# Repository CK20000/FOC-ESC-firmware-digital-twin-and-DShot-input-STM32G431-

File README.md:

# FOC ESC: firmware, digital twin and DShot input (STM32G431)

Sensorless field-oriented control (FOC) firmware for a custom 6S drone ESC, together with a software-in-the-loop (SIL) digital twin that runs the same C code against a simulated motor, inverter and PCB.

**Status:** the firmware and the DShot input have been tested on a bare STM32G431 dev board. The ESC PCB in this repository has passed DFM checks but has not been manufactured yet, so nothing here has been run on a motor.

## What is in this repository

- **Firmware (`Src/`, `Inc/`)**: 48 kHz sensorless FOC with a sliding-mode observer (SMO), a PLL, I-f startup and space vector PWM. The time-critical code runs from CCM RAM.
- **DShot300 receiver (`Src/foc_dshot.c`)**: a raw 32-edge decoder on PA0, written from scratch.
- **Digital twin (`sim/`)**: a C plant model (PMSM, inverter dead-time, Rds(on) drops, battery sag) plus a Python solver for PCB heat and ground bounce, shown in a PyQt6 dashboard.
- **Hardware (KiCad project and Gerbers)**: a 4-layer board (F.Cu, In1.Cu, In2.Cu, B.Cu) built around an STM32G431, an EG2134 gate driver and AD8418 current-sense amplifiers.

## Layout

```text
Inc/
  foc_core.h         FOC API, state machine, debug struct
  foc_dshot.h        DShot API and receiver state
Src/
  foc_core.c         FOC algorithm (SMO, PLL, I-f startup, CCM RAM)
  foc_dshot.c        DShot300 receiver
  main.c             Hardware init, CCM copy routine, flash-readout benchmark
  usb_cdc.c          USB CDC support
sim/
  sil/               Firmware + C plant, built into a shared library
    plant_c.c/.h              plant model
    sim_bridge.c/.h           bridge between the plant and Python
    virtual_stm32.c/.h        x86 stand-in for the MCU
    streaming_scope4.py       PyQt6 dashboard
  hil/               PCB thermal and ground-bounce solvers
    unified_esc_dashboard.py
    pcb_geometry.json
  test_dshot.py, virtual_mcu_dshot.py   DShot decoder tests on a virtual MCU
Makefile.hardware    Builds the .elf/.bin for the STM32G431
foc_g431.ld          Linker script with a CCM RAM section
```

## Quick start: simulation

```bash
cd sim/sil
make clean && make
python3 streaming_scope4.py
```

Press **Play**, raise the **Throttle** slider, and raise the **Speed** slider to speed up the simulation.

## Quick start: hardware

Install the ARM toolchain and a DFU tool:

```bash
sudo apt install gcc-arm-none-eabi dfu-util
```

Build from the folder that contains `Makefile.hardware`:

```bash
make -f Makefile.hardware clean
make -f Makefile.hardware -j4
```

This writes `build_hardware/foc_g431.elf`, `.bin` and `.map`.

Flash over USB DFU:

1. Hold **BOOT0**, tap **RESET**, release **BOOT0**.
2. Under WSL, attach the USB device first (Windows PowerShell, as admin): `usbipd list`, then `usbipd attach --wsl --busid <BUSID>`.
3. Flash:

```bash
sudo dfu-util --device 0483:df11 --alt 0 --dfuse-address 0x08000000:leave --download build_hardware/foc_g431.bin
```

The final `Error during download get_status` message is expected, since the board reboots after flashing.

## Measurements on silicon

`main.c` runs `foc_loop()` for 5 seconds (240,000 iterations), records the worst-case cycle count with the `DWT->CYCCNT` register, and saves a debug record to the last flash page (`0x0801F800`). Read it back with:

```bash
rm -f debug.bin
sudo dfu-util --device 0483:df11 --alt 0 --dfuse-address 0x0801F800:40 --upload debug.bin
hexdump -e '5/4 "%d " "\n"' debug.bin
```

The record is the `DebugInfo` struct in `foc_core.h`:

| Field | Meaning |
| :--- | :--- |
| `magic` | `0xDEADBEEF` if the record is valid |
| `loop_count` | Number of loop iterations run |
| `final_state` | Drive state at the end (0 = OFF, 3 = closed-loop FOC) |
| `throttle_x1000` | Throttle times 1000 (800 means 0.8) |
| `max_cycles` | Worst-case cycles for one loop |

Results so far, both on a dev board with no motor attached:

| Run | Final state | Throttle | Worst-case cycles | Time at 170 MHz |
| :--- | :--- | :--- | :--- | :--- |
| Closed-loop benchmark (forced closed-loop state) | 3 | 0.800 | 1,224 | 7.2 µs |
| DShot input test (DShot command from a flight controller) | 0 (OFF) | 0.480 | 1,162 | 6.8 µs |

The 1,224-cycle figure is the one to use for the closed-loop budget. The DShot run stayed in the OFF state, so its 1,162 cycles do not include the closed-loop control math. What the DShot run shows is that a throttle command sent by a flight controller reached the FOC core.

## DShot300 input

A DShot frame is 16 bits (11 throttle, 1 telemetry request, 4 CRC), which gives 32 edges per frame. At DShot300 each bit lasts 3.33 µs. The decoder on PA0 timestamps each edge with the DWT cycle counter.

Problems found and fixed while testing on the dev board:

- **Wrong frame length.** The first decoder waited for 42 edges and used GCR decoding. GCR is used only for the ESC's replies in bidirectional DShot, so the old decoder spanned two frames. It now decodes the raw 32-edge frame.
- **Clock speed.** The Arduino core ran the chip at 150 MHz, not 170 MHz, so a fixed 0/1 threshold failed. The decoder now measures the bit period and sets the threshold from it.
- **CRC.** With bidirectional DShot enabled, Betaflight inverts the CRC. The decoder accepts both forms.
- **Interrupt priority.** Every second frame collided with the 1 kHz SysTick interrupt, which delayed the edge timestamp. Giving the EXTI edge interrupt a higher priority than SysTick fixed it.

The receiver keeps `frames_ok` and `frames_bad` counters in the `dshot` struct. A complete frame-error measurement over a full throttle sweep is still to be published.

## Simulation features

- **I-f startup:** forces current into the motor and rotates the field to drag the rotor from rest.
- **SMO + PLL:** sensorless angle estimate.
- **Inverter model:** 200 ns dead-time distortion, MOSFET Rds(on) drops, battery sag.
- **Thermal model:** finite-difference heat diffusion across the PCB copper layers, from conduction (I²R) and switching losses based on FET datasheets.
- **Ground bounce:** copper resistance extracted from the layout, with differential ground-bounce errors injected into the ADC measurements.

## Pinout

| Pin | Function | Description |
| :--- | :--- | :--- |
| PA0 | DShot input | From the flight controller |
| PA1 | Phase U | ADC1 current sense |
| PA7 | Phase V | ADC2 current sense |
| PA8 | U high | Gate driver |
| PA9 | V high | Gate driver |
| PA10 | W high | Gate driver |
| PB13 | U low | Gate driver |
| PB14 | V low | Gate driver |
| PB15 | W low | Gate driver |
| PA2 / PA3 | Telemetry TX / RX | USART2 at 2 Mbaud |
| PA13 / PA14 | SWDIO / SWCLK | Debug |

Telemetry is a binary 49-byte struct on USART2. If the board is wired for USART1 on PB6/PB7 instead, switch `MX_USART2_UART_Init` to `MX_USART1_UART_Init` with `GPIO_PIN_6 | GPIO_PIN_7` and `AF7_USART1`.

## Board status and next steps

- The 4-layer PCB has passed DFM checks against JLCPCB capabilities.
- Components are being sourced for the first board.
- Next: assemble the first board, check the DShot timing on PA0 with a scope, and do a current-limited bench bring-up before any motor test.

## Known limits

- The gate driver, current sensing, observer and PLL have not been tested on a real motor.
- The digital twin is only as accurate as its motor and inverter model.
- The dev-board tests used no motor, so the timing figures come from benchmark inputs, not from a spinning rotor.

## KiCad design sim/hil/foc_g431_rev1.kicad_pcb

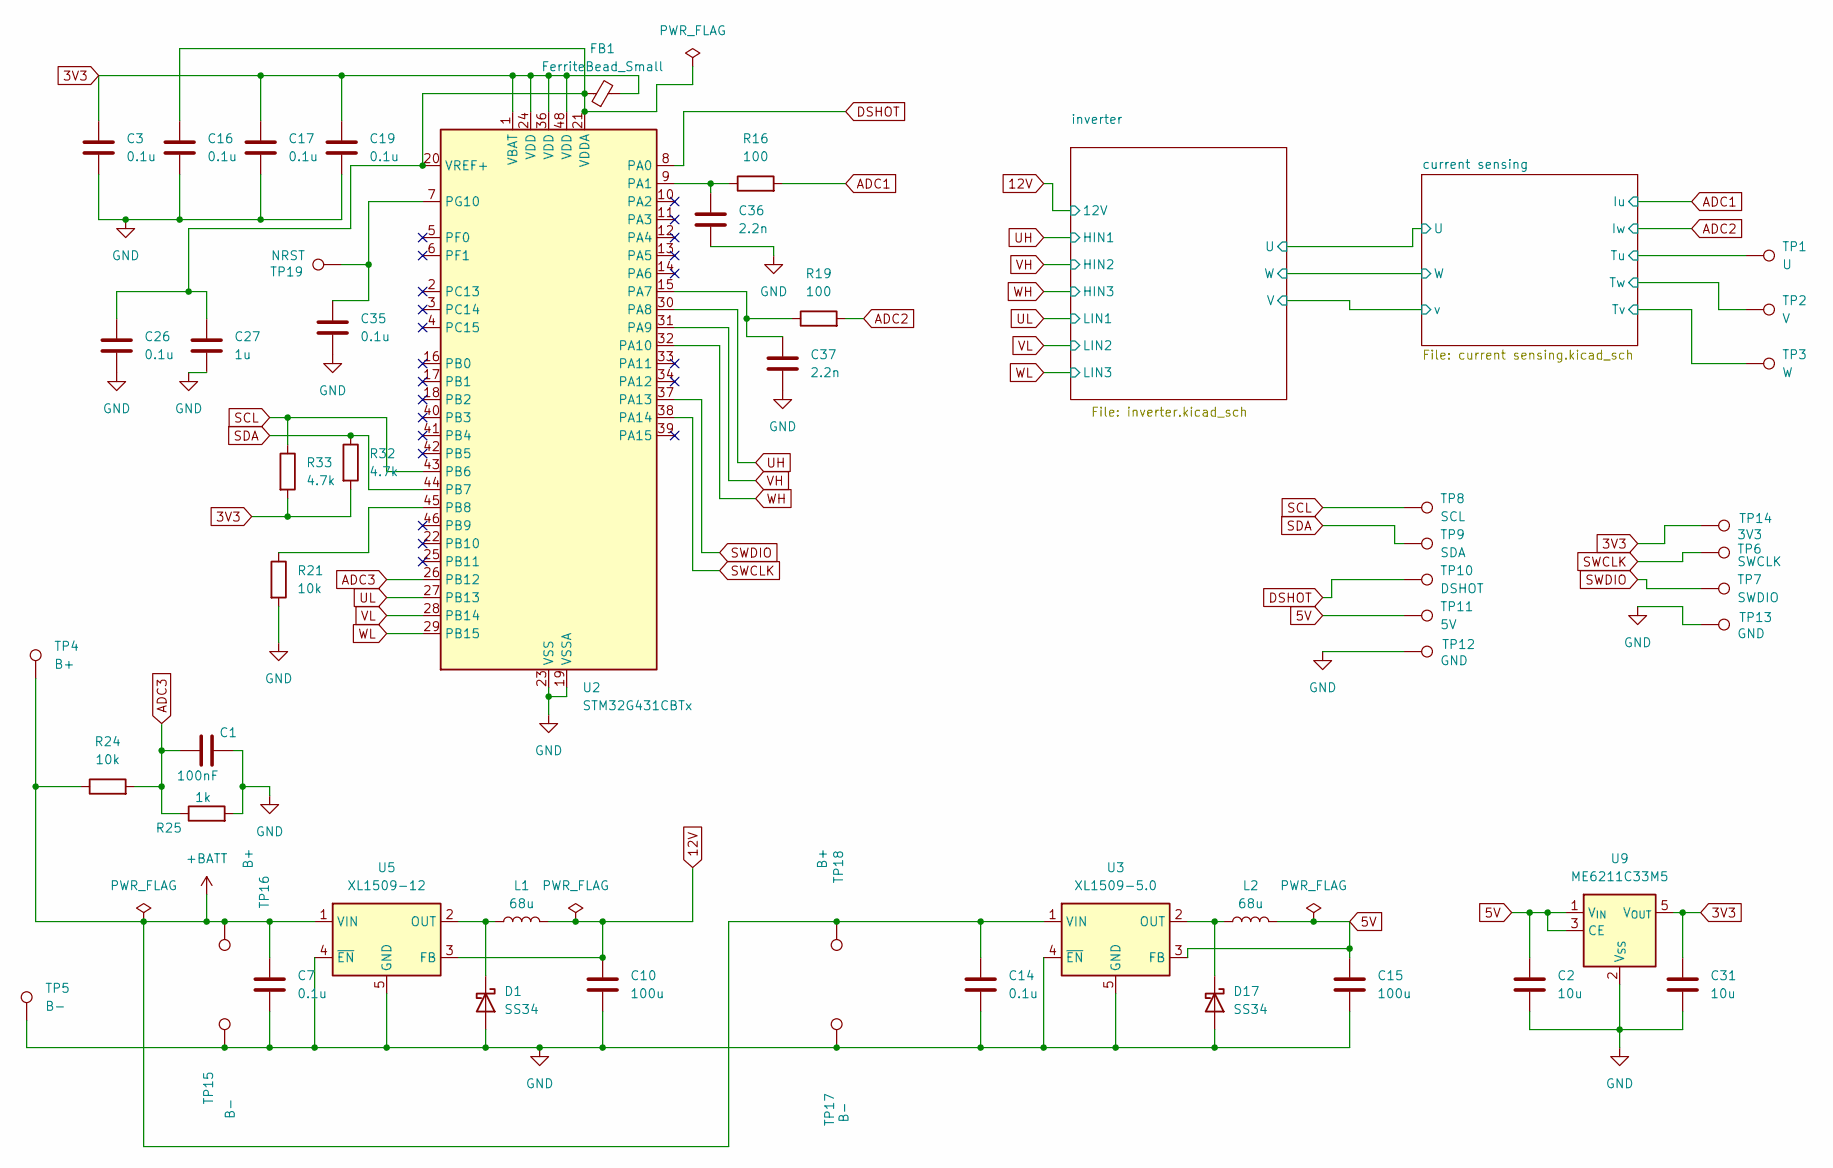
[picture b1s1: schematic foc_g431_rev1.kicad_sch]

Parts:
C1: 100nF; C_0603_1608Metric_Pad1.08x0.95mm_HandSolder
C2, C31: 10u; C_0805_2012Metric_Pad1.18x1.45mm_HandSolder
C3, C7, C14, C16, C17, C19, C26, C35: 0.1u; C_0603_1608Metric_Pad1.08x0.95mm_HandSolder
C10, C15: 100u; CP_EIA-3528-21_Kemet-B_HandSolder
C27: 1u; C_0603_1608Metric_Pad1.08x0.95mm_HandSolder
C36, C37: 2.2n; C_0603_1608Metric_Pad1.08x0.95mm_HandSolder
D1, D17: SS34; D_SMA
FB1: FerriteBead_Small; L_0805_2012Metric_Pad1.05x1.20mm_HandSolder
L1, L2: 68u; L_APV_APH0630
R16, R19: 100; R_0805_2012Metric_Pad1.20x1.40mm_HandSolder
R21, R24: 10k; R_0603_1608Metric_Pad0.98x0.95mm_HandSolder
R25: 1k; R_0603_1608Metric_Pad0.98x0.95mm_HandSolder
R32, R33: 4.7k; R_0603_1608Metric_Pad0.98x0.95mm_HandSolder
TP1: U; TestPoint_Pad_1.0x1.0mm
TP2: V; TestPoint_Pad_1.0x1.0mm
TP3: W; TestPoint_Pad_1.0x1.0mm
TP4, TP16, TP18: B+; TestPoint_Pad_1.0x1.0mm
TP5, TP15, TP17: B-; TestPoint_Pad_1.0x1.0mm
TP6: SWCLK; TestPoint_Pad_1.0x1.0mm
TP7: SWDIO; TestPoint_Pad_1.0x1.0mm
TP8: SCL; TestPoint_Pad_1.0x1.0mm
TP9: SDA; TestPoint_Pad_1.0x1.0mm
TP10: DSHOT; TestPoint_Pad_1.0x1.0mm
TP11: 5V; TestPoint_Pad_1.0x1.0mm
TP12, TP13: GND; TestPoint_Pad_1.0x1.0mm
TP14: 3V3; TestPoint_Pad_1.0x1.0mm
TP19: NRST; TestPoint_Pad_1.0x1.0mm
U2: STM32G431CBTx; LQFP-48_7x7mm_P0.5mm
U3: XL1509-5.0; SOIC-8_3.9x4.9mm_P1.27mm
U5: XL1509-12; SOIC-8_3.9x4.9mm_P1.27mm
U9: ME6211C33M5; SOT-23-5

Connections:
3V3: C3.1, C17.1, C19.1, C31.1, FB1.2, R32.2, R33.2, TP14.1, U2.1 (VBAT), U2.24 (VDD), U2.36 (VDD), U2.48 (VDD), U9.5 (V_{OUT}); also elsewhere on the board
5V: C2.1, C15.1, L2.2, TP11.1, U3.3 (FB), U9.1 (V_{IN}), U9.3 (CE)
12V: C10.1, L1.2, U5.3 (FB); also elsewhere on the board
+BATT: C7.1, C14.1, R24.1, TP4.1, TP16.1, TP18.1, U3.1 (VIN), U5.1 (VIN); also elsewhere on the board
/current sensing/Tu: TP1.1; also elsewhere on the board
/current sensing/Tv: TP3.1; also elsewhere on the board
/current sensing/Tw: TP2.1; also elsewhere on the board
ADC1: R16.2; also elsewhere on the board
ADC2: R19.2; also elsewhere on the board
ADC3: C1.2, R24.2, R25.1, U2.26 (PB12)
DSHOT: TP10.1, U2.8 (PA0)
GND: C1.1, C2.2, C3.2, C7.2, C10.2, C14.2, C15.2, C16.2, C17.2, C19.2, C26.2, C27.2, C31.2, C35.2, C36.2, C37.2, D1.2 (A), D17.2 (A), R21.2, R25.2, TP5.1, TP12.1, TP13.1, TP15.1, TP17.1, U2.19 (VSSA), U2.23 (VSS), U2.35 (VSS), U2.47 (VSS), U3.4 (~EN), U3.5 (GND), U3.6 (GND), U3.7 (GND), U3.8 (GND), U5.4 (~EN), U5.5 (GND), U5.6 (GND), U5.7 (GND), U5.8 (GND), U9.2 (V_{SS}); also elsewhere on the board
unnamed: D1.1 (K), L1.1, U5.2 (OUT)
unnamed: D17.1 (K), L2.1, U3.2 (OUT)
unnamed: C36.1, R16.1, U2.9 (PA1)
unnamed: C37.1, R19.1, U2.15 (PA7)
unnamed: R21.1, U2.45 (PB8)
unnamed: C35.1, TP19.1, U2.7 (PG10)
unnamed: C16.1, C26.1, C27.1, FB1.1, U2.20 (VREF+), U2.21 (VDDA)
SCL: R33.1, TP8.1, U2.43 (PB6)
SDA: R32.1, TP9.1, U2.44 (PB7)
SWCLK: TP6.1, U2.38 (PA14)
SWDIO: TP7.1, U2.37 (PA13)
UH: U2.30 (PA8); also elsewhere on the board
UL: U2.27 (PB13); also elsewhere on the board
VH: U2.31 (PA9); also elsewhere on the board
VL: U2.28 (PB14); also elsewhere on the board
WH: U2.32 (PA10); also elsewhere on the board
WL: U2.29 (PB15); also elsewhere on the board

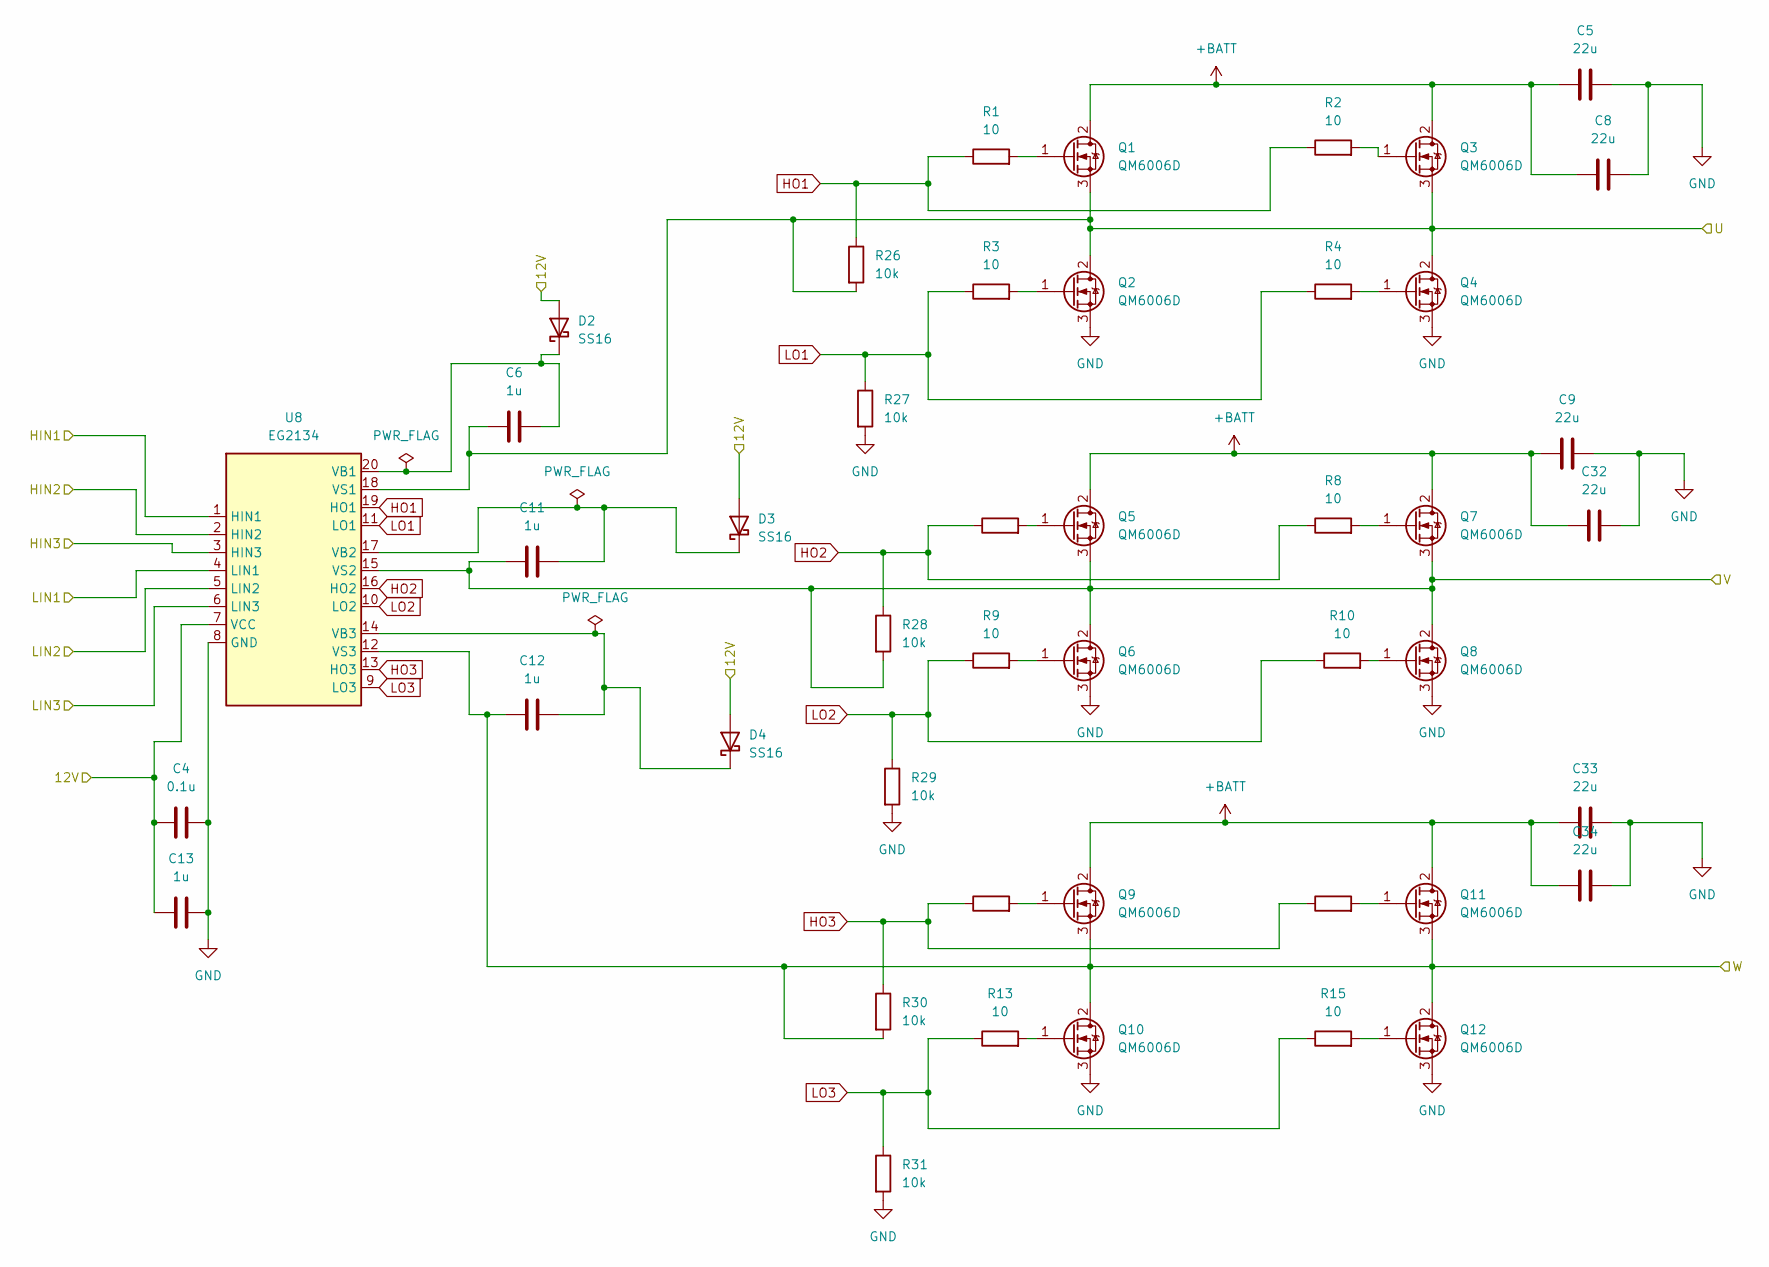
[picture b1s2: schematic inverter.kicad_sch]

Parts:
C4: 0.1u; C_0603_1608Metric_Pad1.08x0.95mm_HandSolder
C5, C8, C9, C32, C33, C34: 22u; C_1206_3216Metric_Pad1.33x1.80mm_HandSolder
C6, C11, C12, C13: 1u; C_0603_1608Metric_Pad1.08x0.95mm_HandSolder
D2, D3, D4: SS16; D_SMA
Q1, Q2, Q3, Q4, Q5, Q6, Q7, Q8, Q9, Q10, Q11, Q12: QM6006D; TO-252-2
R1, R2, R3, R4, R7, R8, R9, R10, R11, R12, R13, R15: 10; R_0603_1608Metric_Pad0.98x0.95mm_HandSolder
R26, R27, R28, R29, R30, R31: 10k; R_0603_1608Metric_Pad0.98x0.95mm_HandSolder
U8: EG2134; TSSOP-20_4.4x6.5mm_P0.65mm

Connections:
12V: C4.1, C13.2, D2.2 (A), D3.2 (A), D4.2 (A), U8.7 (VCC); also elsewhere on the board
+BATT: C5.1, C8.1, C9.1, C32.1, C33.1, C34.1, Q1.2 (D), Q3.2 (D), Q5.2 (D), Q7.2 (D), Q9.2 (D), Q11.2 (D); also elsewhere on the board
/current sensing/Tv: C11.1, Q5.3 (S), Q6.2 (D), Q7.3 (S), Q8.2 (D), R28.2, U8.15 (VS2); also elsewhere on the board
/current sensing/U: C6.2, Q1.3 (S), Q2.2 (D), Q3.3 (S), Q4.2 (D), R26.2, U8.18 (VS1); also elsewhere on the board
/current sensing/W: C12.1, Q9.3 (S), Q10.2 (D), Q11.3 (S), Q12.2 (D), R30.2, U8.12 (VS3); also elsewhere on the board
GND: C4.2, C5.2, C8.2, C9.2, C13.1, C32.2, C33.2, C34.2, Q2.3 (S), Q4.3 (S), Q6.3 (S), Q8.3 (S), Q10.3 (S), Q12.3 (S), R27.2, R29.2, R31.2, U8.8 (GND); also elsewhere on the board
HO1: R1.1, R2.1, R26.1, U8.19 (HO1)
HO2: R7.1, R8.1, R28.1, U8.16 (HO2)
HO3: R11.1, R12.1, R30.1, U8.13 (HO3)
LO1: R3.1, R4.1, R27.1, U8.11 (LO1)
LO2: R9.1, R10.1, R29.1, U8.10 (LO2)
LO3: R13.1, R15.1, R31.1, U8.9 (LO3)
unnamed: C6.1, D2.1 (K), U8.20 (VB1)
unnamed: C11.2, D3.1 (K), U8.17 (VB2)
unnamed: C12.2, D4.1 (K), U8.14 (VB3)
unnamed: Q1.1 (G), R1.2
unnamed: Q2.1 (G), R3.2
unnamed: Q3.1 (G), R2.2
unnamed: Q4.1 (G), R4.2
unnamed: Q5.1 (G), R7.2
unnamed: Q6.1 (G), R9.2
unnamed: Q7.1 (G), R8.2
unnamed: Q8.1 (G), R10.2
unnamed: Q9.1 (G), R11.2
unnamed: Q10.1 (G), R13.2
unnamed: Q11.1 (G), R12.2
unnamed: Q12.1 (G), R15.2
UH: U8.1 (HIN1); also elsewhere on the board
UL: U8.4 (LIN1); also elsewhere on the board
VH: U8.2 (HIN2); also elsewhere on the board
VL: U8.5 (LIN2); also elsewhere on the board
WH: U8.3 (HIN3); also elsewhere on the board
WL: U8.6 (LIN3); also elsewhere on the board

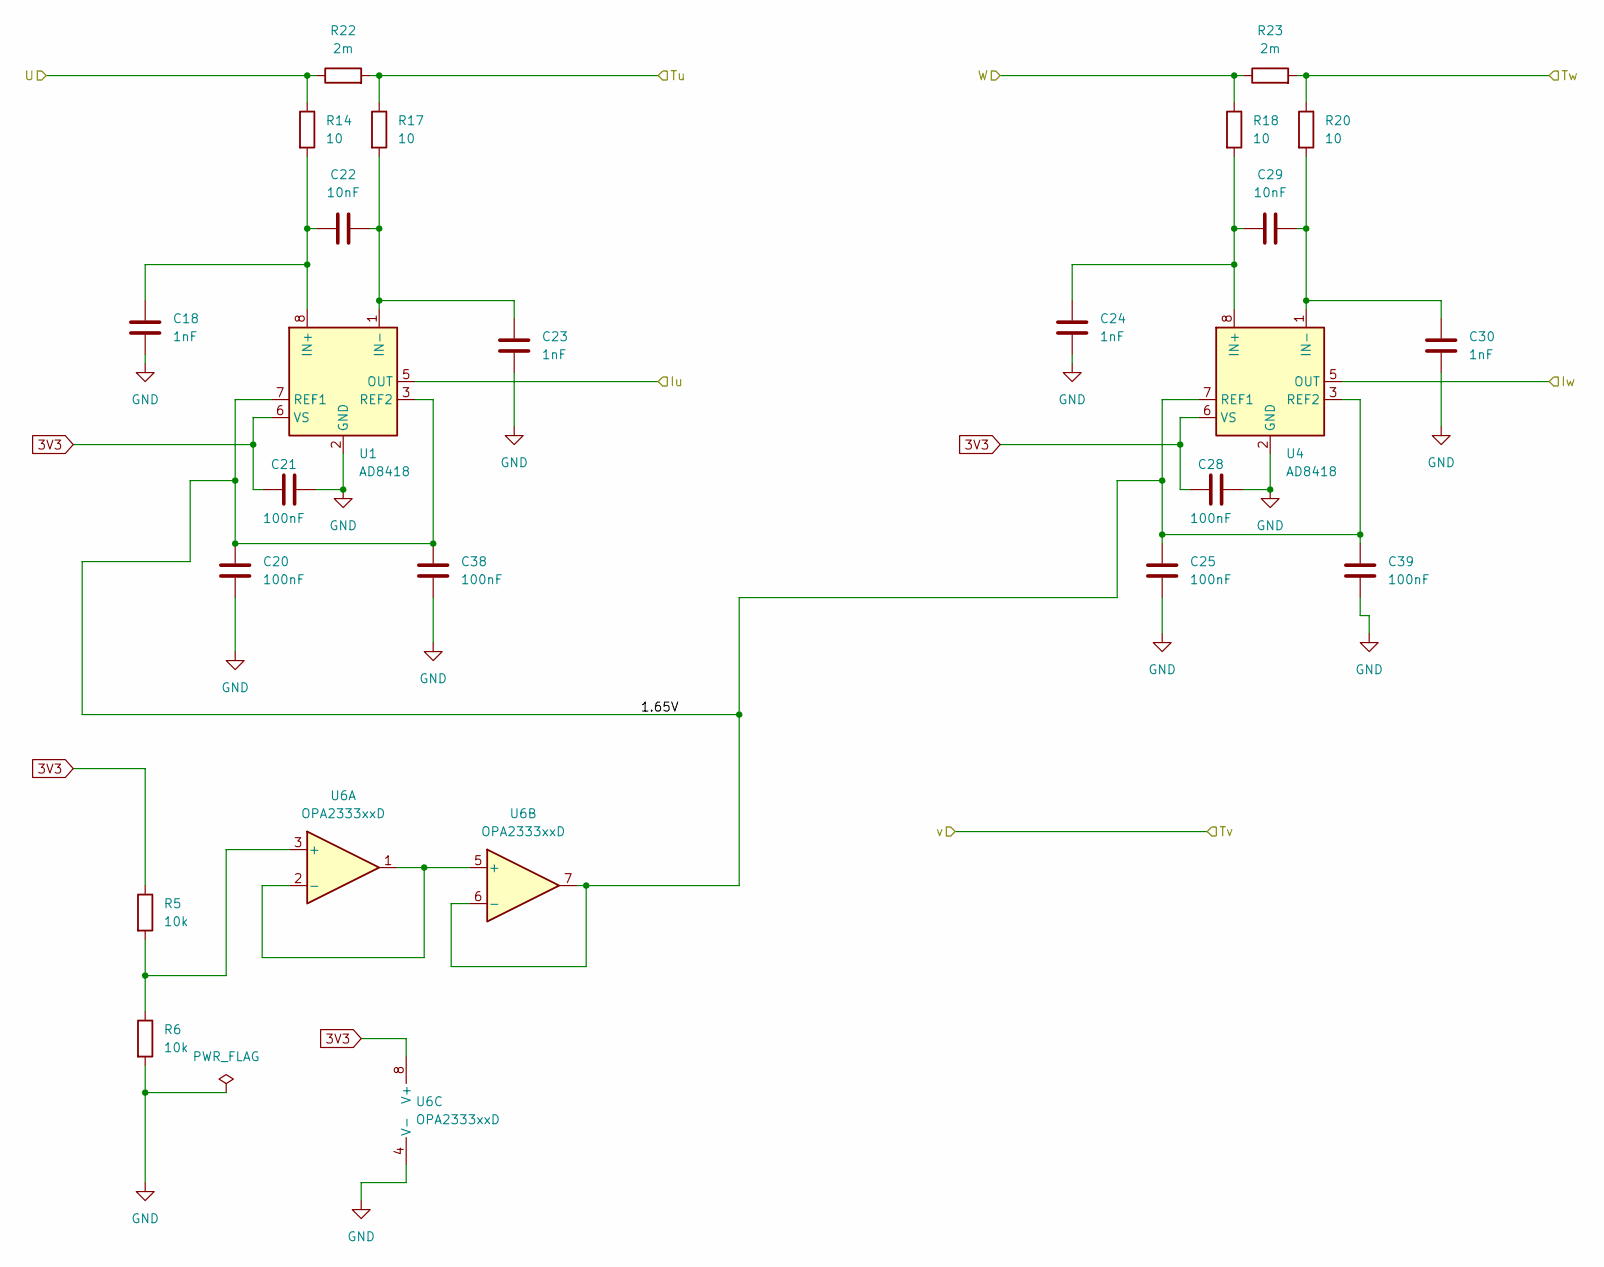
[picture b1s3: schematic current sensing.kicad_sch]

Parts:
C18, C23, C24, C30: 1nF; C_0603_1608Metric_Pad1.08x0.95mm_HandSolder
C20, C21, C25, C28, C38, C39: 100nF; C_0603_1608Metric_Pad1.08x0.95mm_HandSolder
C22, C29: 10nF; C_0603_1608Metric_Pad1.08x0.95mm_HandSolder
R5, R6: 10k; R_0603_1608Metric_Pad0.98x0.95mm_HandSolder
R14, R17, R18, R20: 10; R_0603_1608Metric_Pad0.98x0.95mm_HandSolder
R22, R23: 2m; R_4020_10251Metric_Pad1.65x5.30mm_HandSolder
U1, U4: AD8418; SOIC-8_3.9x4.9mm_P1.27mm
U6: OPA2333xxD; MSOP-8_3x3mm_P0.65mm

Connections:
3V3: C21.2, C28.2, R5.1, U1.6 (VS), U4.6 (VS), U6.8 (V+); also elsewhere on the board
/current sensing/1.65V: C20.1, C25.1, C38.1, C39.1, U1.3 (REF2), U1.7 (REF1), U4.3 (REF2), U4.7 (REF1), U6.6 (-), U6.7
/current sensing/Tu: R17.1, R22.2; also elsewhere on the board
/current sensing/Tw: R20.1, R23.2; also elsewhere on the board
/current sensing/U: R14.1, R22.1; also elsewhere on the board
/current sensing/W: R18.1, R23.1; also elsewhere on the board
ADC1: U1.5 (OUT); also elsewhere on the board
ADC2: U4.5 (OUT); also elsewhere on the board
GND: C18.2, C20.2, C21.1, C23.2, C24.2, C25.2, C28.1, C30.2, C38.2, C39.2, R6.2, U1.2 (GND), U4.2 (GND), U6.4 (V-); also elsewhere on the board
unnamed: C18.1, C22.2, R14.2, U1.8 (IN+)
unnamed: C22.1, C23.1, R17.2, U1.1 (IN-)
unnamed: C24.1, C29.2, R18.2, U4.8 (IN+)
unnamed: C29.1, C30.1, R20.2, U4.1 (IN-)
unnamed: R5.2, R6.1, U6.3 (+)
unnamed: U6.1, U6.2 (-), U6.5 (+)

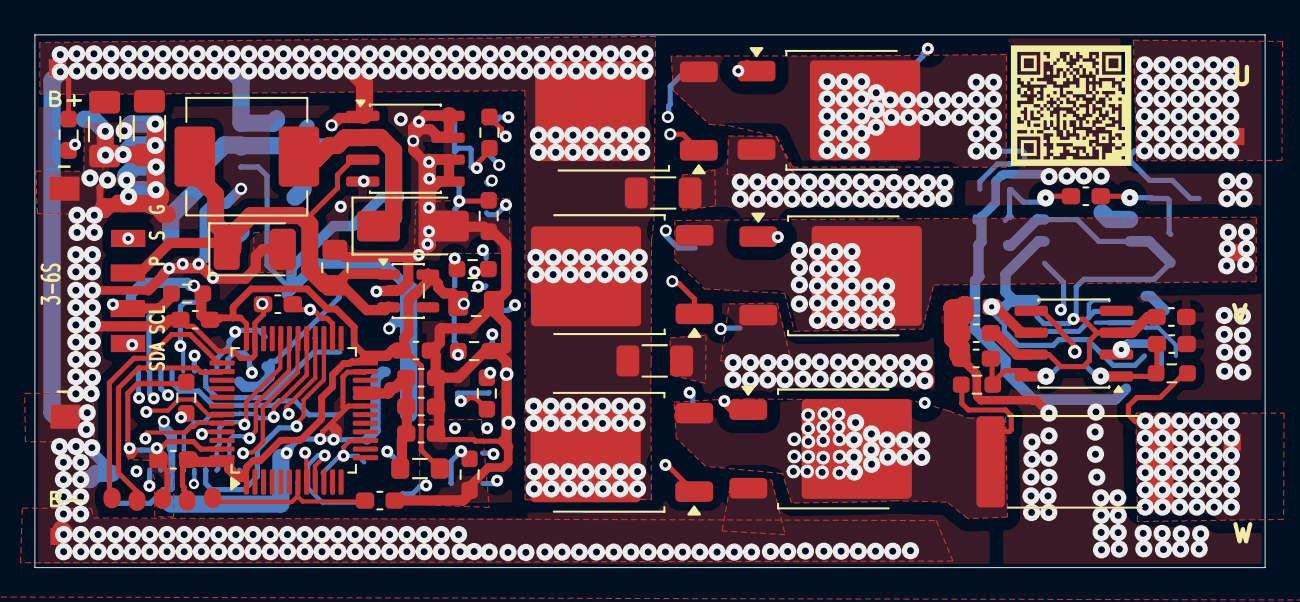
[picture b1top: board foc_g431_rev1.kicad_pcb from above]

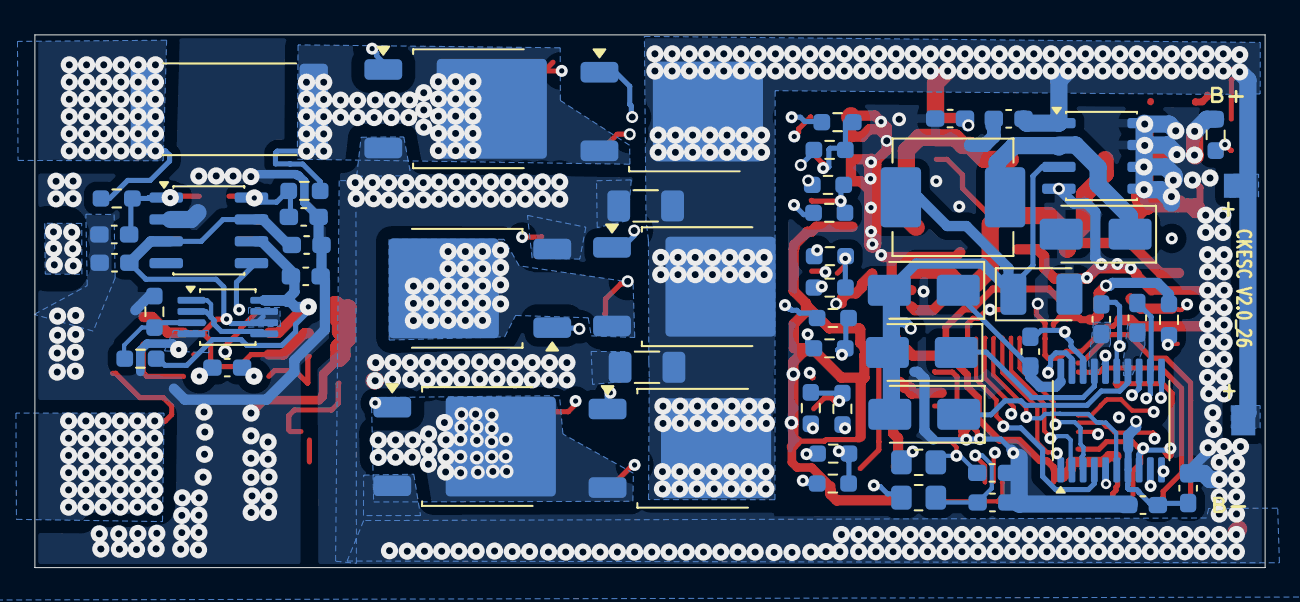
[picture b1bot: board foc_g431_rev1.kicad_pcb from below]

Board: 6 copper layers, 71.4 x 30.9 mm, 119 parts (56 on the bottom side), 59 nets.
